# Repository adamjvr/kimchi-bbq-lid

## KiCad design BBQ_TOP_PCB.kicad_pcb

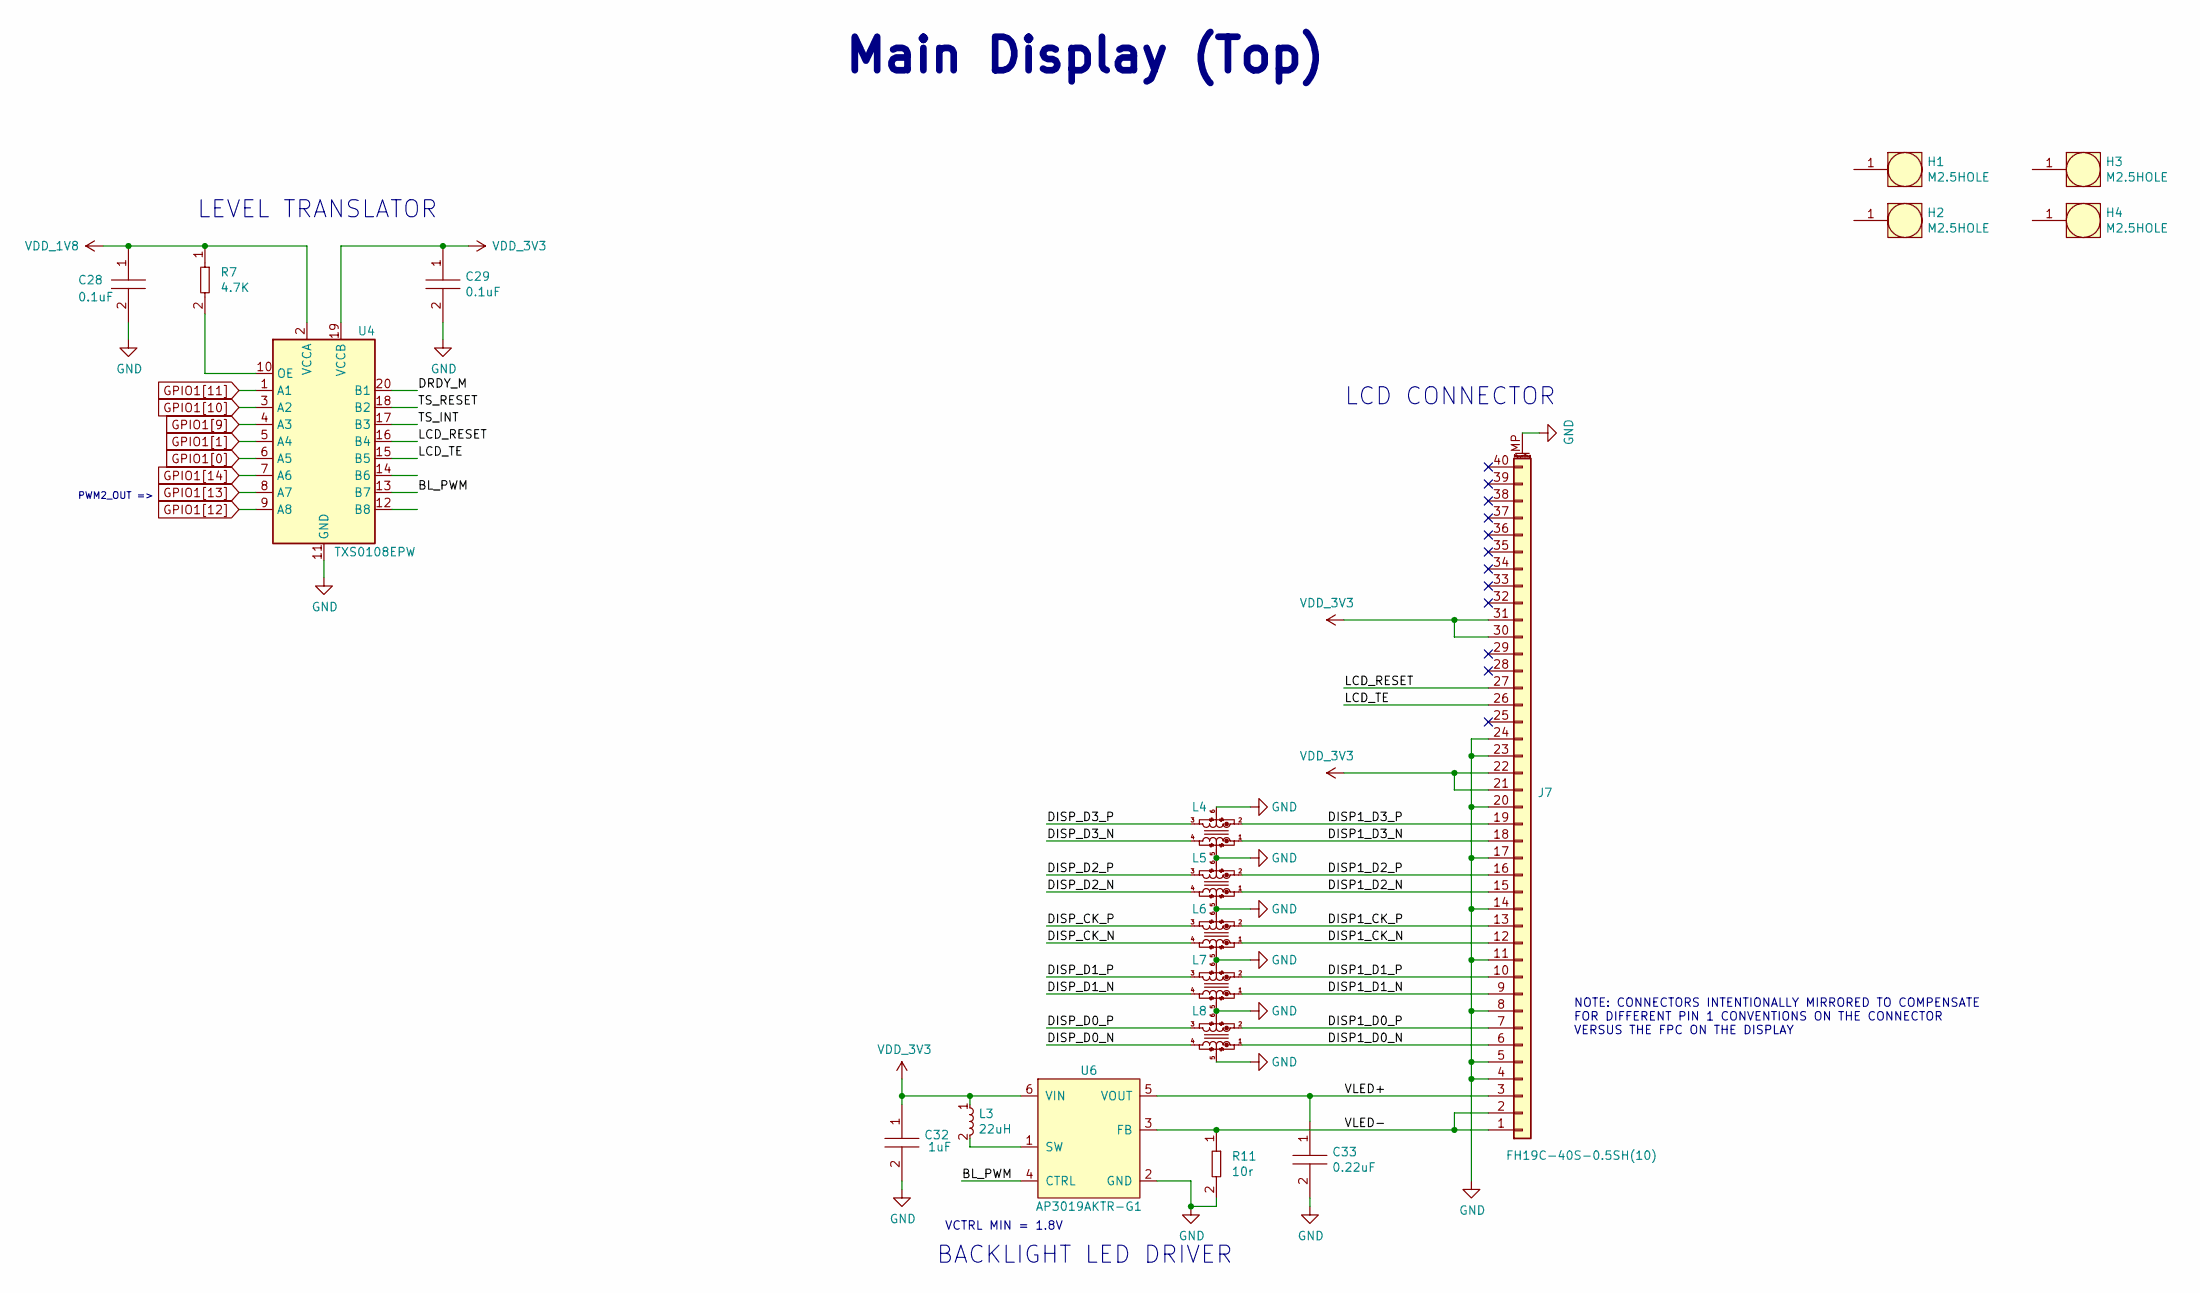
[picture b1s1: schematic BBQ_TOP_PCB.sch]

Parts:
C28, C29: C0603C104M5RACAUTO; C0603; Tolerance 20%; Voltage 50V; MFR# C0603C104M5RACAUTO
C32: C0603C105K4PAC7411; C0603; Tolerance 20%; Voltage 16V; MFR# C0603C105K4PAC7411
C33: CGA3E3X7R1H224K080AB; C0603; Tolerance 10%; Voltage 50V; MFR# CGA3E3X7R1H224K080AB
H1, H2, H3, H4: M2.5HOLE
J7: FH19C-40S-0.5SH(10); HRS_FH19C-40S-0.5SH_1x40-1MP_P0.50mm; Part FH19C-40S-0.5SH(10)
L3: TYA4012220M-10; L_Taiyo-Yuden_MD-4040; Tolerance *; Voltage *; MFR# TYA4012220M-10
L4, L5, L6, L7, L8: LCFE121002; Part LCFE121002
R7: RC0603JR-074K7L; R0603; Tolerance 1%; Voltage *; MFR# RC0603JR-074K7L
R11: RE0603FRE0710RL; R0603; Tolerance 1%; Voltage *; MFR# RE0603FRE0710RL
U4: TXS0108EPW; TXS0108EPWR; Part TXS0108EPW
U6: AP3019AKTR-G1; SOT-23-6_Handsoldering; Part AP3019AKTR-G1

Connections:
/BL_PWM: U4.13 (B7), U6.4 (CTRL)
/DISP1_CK_N: J7.12, L6.1
/DISP1_CK_P: J7.13, L6.2
/DISP1_D0_N: J7.6, L8.1
/DISP1_D0_P: J7.7, L8.2
/DISP1_D1_N: J7.9, L7.1
/DISP1_D1_P: J7.10, L7.2
/DISP1_D2_N: J7.15, L5.1
/DISP1_D2_P: J7.16, L5.2
/DISP1_D3_N: J7.18, L4.1
/DISP1_D3_P: J7.19, L4.2
/DISP_CK_N: L6.4
/DISP_CK_P: L6.3
/DISP_D0_N: L8.4
/DISP_D0_P: L8.3
/DISP_D1_N: L7.4
/DISP_D1_P: L7.3
/DISP_D2_N: L5.4
/DISP_D2_P: L5.3
/DISP_D3_N: L4.4
/DISP_D3_P: L4.3
/DRDY_M: U4.20 (B1)
/LCD_RESET: J7.27, U4.16 (B4)
/LCD_TE: J7.26, U4.15 (B5)
/TS_INT: U4.17 (B3)
/TS_RESET: U4.18 (B2)
/VLED+: C33.1, J7.3, U6.5 (VOUT)
/VLED-: J7.1, J7.2, R11.1, U6.3 (FB)
GND: C28.2, C29.2, C32.2, C33.2, J7.4, J7.5, J7.8, J7.11, J7.14, J7.17, J7.20, J7.23, J7.24, J7.MP (MountPin), L4.5, L4.6 (5), L5.5, L5.6 (5), L6.5, L6.6 (5), L7.5, L7.6 (5), L8.5, L8.6 (5), R11.2, U4.11 (GND), U6.2 (GND)
GPIO1[0]: U4.6 (A5)
GPIO1[1]: U4.5 (A4)
GPIO1[9]: U4.4 (A3)
GPIO1[10]: U4.3 (A2)
GPIO1[11]: U4.1 (A1)
GPIO1[12]: U4.9 (A8)
GPIO1[13]: U4.8 (A7)
GPIO1[14]: U4.7 (A6)
unnamed: L3.2, U6.1 (SW)
unnamed: R7.2, U4.10 (OE)
VDD_1V8: C28.1, R7.1, U4.2 (VCCA)
VDD_3V3: C29.1, C32.1, J7.21, J7.22, J7.30, J7.31, L3.1, U4.19 (VCCB), U6.6 (VIN)

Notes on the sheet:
BACKLIGHT LED DRIVER
VCTRL MIN = 1.8V
LCD CONNECTOR
NOTE: CONNECTORS INTENTIONALLY MIRRORED TO COMPENSATE FOR DIFFERENT PIN 1 CONVENTIONS ON THE CONNECTOR VERSUS THE FPC ON THE DISPLAY
LEVEL TRANSLATOR
PWM2_OUT =>
Main Display (Top)

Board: 2 copper layers, 19 parts (15 on the bottom side), 20 nets, no tracks yet.

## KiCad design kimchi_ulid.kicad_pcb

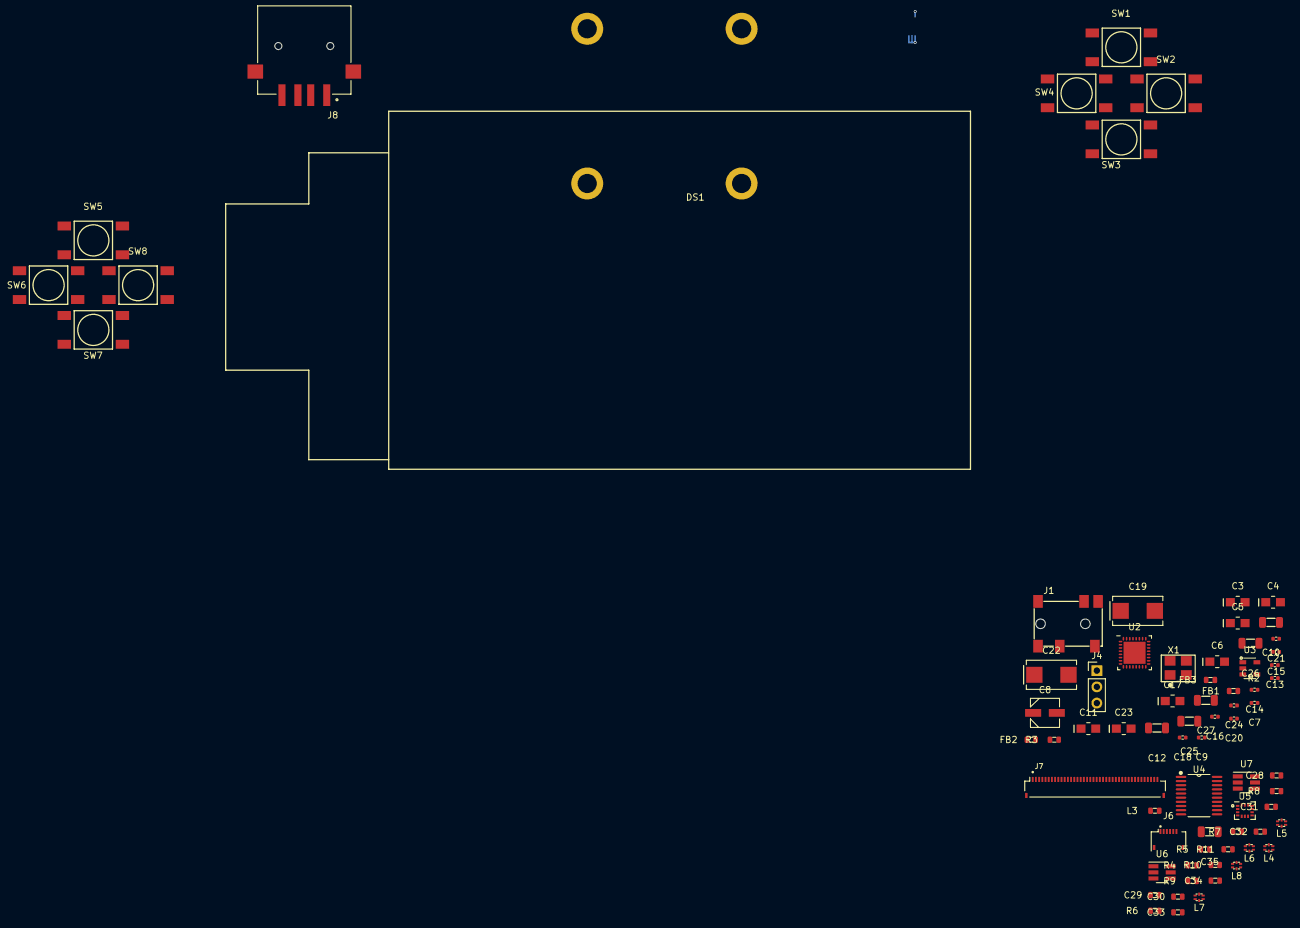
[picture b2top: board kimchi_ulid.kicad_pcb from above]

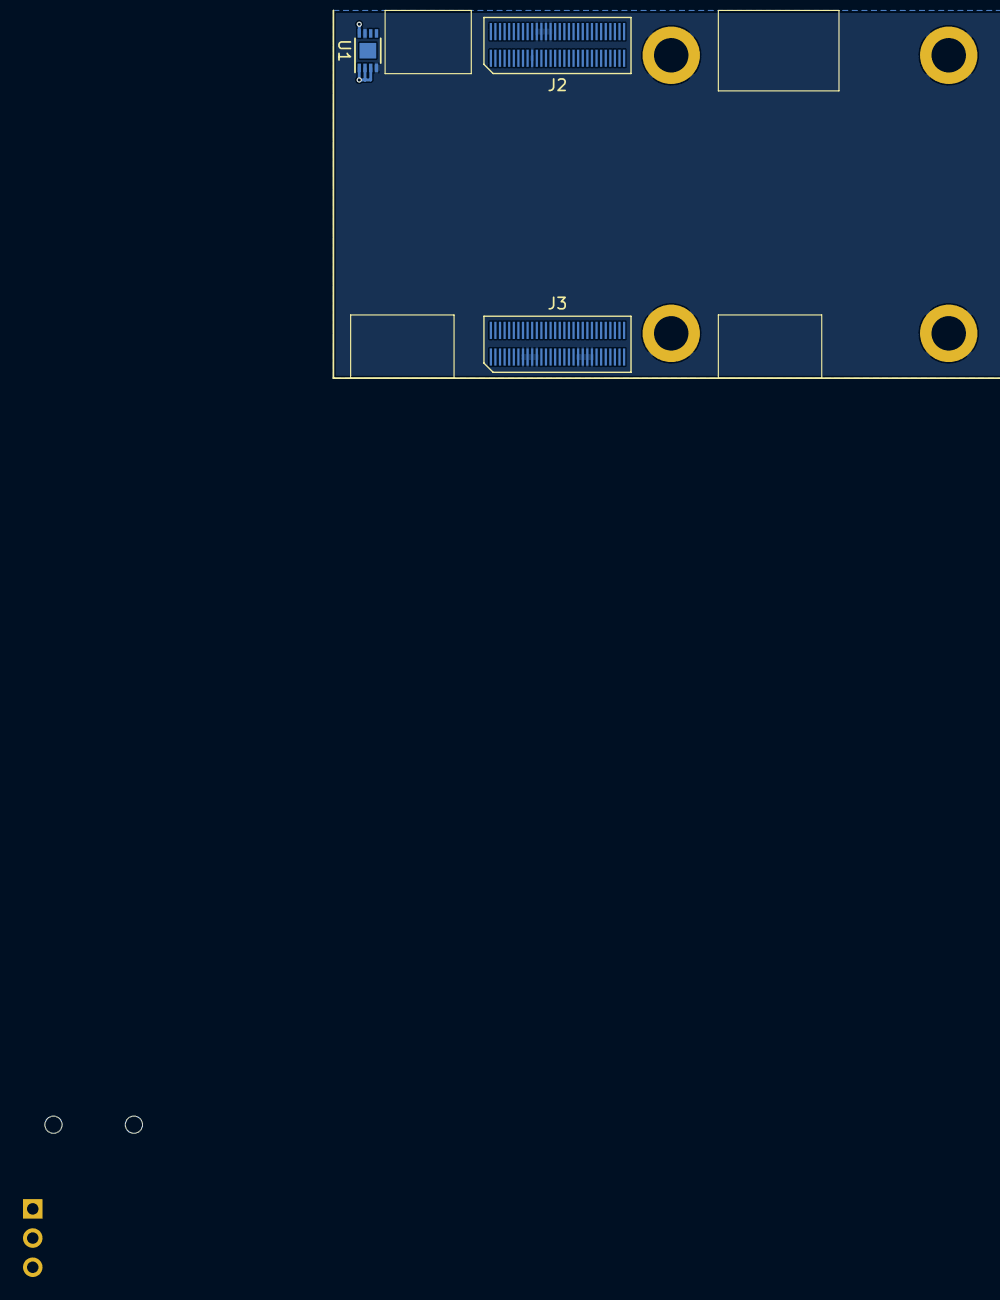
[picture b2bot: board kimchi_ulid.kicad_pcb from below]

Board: 4 copper layers, 83 parts (6 on the bottom side), 69 nets.

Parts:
C3, C4, C5, C6, C11, C17, C23: T494A106M006AT
C7, C9, C13, C14, C15, C16, C18, C20, C21, C24: C0402C104K9PACTU; C0402
C8: UZP1H0R1MCL1GB
C10, C12, C25, C26, C27: T491A105K010AT; C1206
C19, C22: T491D227M010AT
C28, C29, C30, C34: C0603C104M5RACAUTO; C0603
C31: CL10A106MP8NNNC; C0603
C32: C0603C105K4PAC7411; C0603
C33: CGA3E3X7R1H224K080AB; C0603
C35: CC1206MKX5R5BB107; C1206
DS1: ER-TFT035-6; ER-TFT035-6_LCD_DISPLAY
FB1, FB2, FB3: FBMJ1608HM180NTR; R0603
H1, H2, H3, H4: MountingHole_Pad; MountingHole_3mm_Pad
J1: 54-00177
J2, J3: DF40HC(3.5)-60DS
J4: Conn_01x03_Male; Pin_Header_Straight_1x03_Pitch2.54mm
J6: H19C-6S-0.5SH; HRS_FH19C-6S-0.5SH_1x06-1MP_P0.50mm
J7: FH19C-40S-0.5SH(10); HRS_FH19C-40S-0.5SH_1x40-1MP_P0.50mm
J8: 1-292303-6; TE_1-292303-6
L1: GG_LOGO; groupgets_logo
L2: OSHPARK_LOGO; oshpark_logo
L3: TYA4012220M-10; R0603
L4, L5, L6, L7, L8: LCFE121002
LOGO1: Logo_Open_Hardware_Small; OSHW-Logo_5.7x6mm_SilkScreen
R2: RC0402JR-072K2L; R0402
R3: RC0603FR-0747KL; R0603
R4, R5, R6, R7, R8, R9, R10: RC0603JR-074K7L; R0603
R11: RE0603FRE0710RL; R0603
SW1, SW2, SW3, SW4, SW5, SW6, SW7, SW8: TL3301NF260QG
U1: 24C32; DFN-8-1EP_3x2mm_P0.5mm_EP1.36x1.46mm
U2: WM8750CJLGEFL; QFN-32_EP_5x5_Pitch0.5mm
U3: SN74LV1T34DBVRG4; SOT-23-5
U4: TXS0108EPW; TXS0108EPWR
U5: LSM6DSRTR
U6: AP3019AKTR-G1; SOT-23-6_Handsoldering
U7: TPD3S014; SOT-23-6_Handsoldering
X1: ASFL1-12.288MHZ-EC-T; ASFL1

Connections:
/Main Display /BL_PWM: U4.13, U6.4
/Main Display /DISP1_CK_N: J7.12, L6.1
/Main Display /DISP1_CK_P: J7.13, L6.2
/Main Display /DISP1_D0_N: J7.6, L8.1
/Main Display /DISP1_D0_P: J7.7, L8.2
/Main Display /DISP1_D1_N: J7.9, L7.1
/Main Display /DISP1_D1_P: J7.10, L7.2
/Main Display /DISP1_D2_N: J7.15, L5.1
/Main Display /DISP1_D2_P: J7.16, L5.2
/Main Display /DISP1_D3_N: J7.18, L4.1
/Main Display /DISP1_D3_P: J7.19, L4.2
/Main Display /INT1A_G: U4.12, U5.9
/Main Display /INT_M: U4.14, U5.4
/Main Display /LCD_RESET: J7.27, U4.16
/Main Display /LCD_TE: J7.26, U4.15
/Main Display /TS_INT: J6.3, U4.17
/Main Display /TS_RESET: J6.4, U4.18
/Main Display /VLED+: C33.1, J7.3, U6.5
/Main Display /VLED-: J7.1, J7.2, R11.1, U6.3
GND: C3.2, C4.2, C5.2, C6.2, C7.2, C8.2, C9.2, C11.2, C13.2, C14.2, C15.2, C16.2, C17.2, C18.2, C20.2, C21.2, C23.2, C24.2, C28.2, C29.2, C30.2, C31.2, C32.2, C33.2, C34.2, C35.2, FB3.1, H1.1, H2.1, H3.1, H4.1, J2.11, J2.12, J2.13, J2.14, J2.51, J3.38, J3.39, J3.40, J3.41, J3.50, J3.51, J3.52, J3.53, J6.1, J6.MP, J7.4, J7.5, J7.8, J7.11, J7.14, J7.17, J7.20, J7.23, J7.24, J7.MP, J8.4, J8.SH1, J8.SH2, L4.5, L4.6, L5.5, L5.6, L6.5, L6.6, L7.5, L7.6, L8.5, L8.6, R3.1, R11.2, U1.4, U1.7, U2.4, U2.14, U2.19, U2.29, U2.33, U3.3, U4.11, U5.6, U5.7, U6.2, U7.2, X1.2
GPIO1[0]: J3.30, U4.6
GPIO1[1]: J3.29, U4.5
GPIO1[9]: J3.28, U4.4
GPIO1[10]: J3.27, U4.3
GPIO1[11]: J3.26, U4.1
GPIO1[12]: J3.25, U4.9
GPIO1[13]: J3.24, U4.8
GPIO1[14]: J3.23, U4.7
I2C3_SCL: J2.18, J6.5, R10.2, U2.32, U5.13
I2C3_SDA: J2.17, J6.6, R9.2, U2.31, U5.14
I2C4_SCL: J2.16, U1.6
I2C4_SDA: J2.15, U1.5
MCLK: J4.3, U3.4
MIC_BIAS: C9.1, C11.1, R2.2, U2.22
MIC_IN: C25.1, U2.23
unnamed: C10.1, U2.28
unnamed: C12.1, U2.27
unnamed: C15.1, C17.1, U2.21
unnamed: C19.1, U2.13
unnamed: C19.2, J1.4
unnamed: C20.1, C23.1, U2.20
unnamed: C22.1, U2.12
unnamed: C22.2, J1.3
unnamed: C25.2, J1.2, R2.1, R3.2
unnamed: C26.1, U2.16
unnamed: C27.1, U2.15
unnamed: FB3.2, J1.1
unnamed: J4.2, U2.1
unnamed: L3.2, U6.1
unnamed: R4.2, U5.2
unnamed: R5.2, U5.3
unnamed: R6.2, U5.1
unnamed: R7.2, U4.10
unnamed: R8.2, U5.12
unnamed: U3.2, X1.3
SAI3_MCLK: J3.37, J4.1
SAI3_RXD: J3.33, U2.8
SAI3_RXFS: J3.34, U2.9
SAI3_TXC: J3.31, U2.5
SAI3_TXD: J3.32, U2.6
SAI3_TXFS: J3.36, U2.7
USB2_DN: J2.59, J8.2, U7.6
USB2_DP: J2.60, J8.3, U7.5
VBUS: C35.1, J8.1, U7.4
VDD: C6.1, C7.1, C13.1, C18.1, C21.1, C24.1, FB2.2, U2.2, U2.3, U3.5, X1.4
VDDA: C5.1, C8.1, C14.1, C16.1, FB1.2, U2.17, U2.18
VDD_1V8: C28.1, J3.42, J3.43, J3.44, J3.45, R7.1, U4.2
VDD_3V3: C3.1, C4.1, C29.1, C30.1, C31.1, C32.1, FB1.1, FB2.1, J3.54, J3.55, J3.56, J3.57, J6.2, J7.21, J7.22, J7.30, J7.31, L3.1, R4.1, R5.1, R6.1, R8.1, R9.1, R10.1, U1.1, U1.2, U1.3, U1.8, U4.19, U5.5, U5.8, U6.6
VDD_5V: C34.1, J2.7, J2.8, J2.9, J2.10, U7.1, U7.3

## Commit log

2020-12-10 added resistors for codec, transferring workstations
2020-12-11 Oscillator Circuit
    Oscillator circuit and related components added to the codec circuit. These may be unnecessary but are pending review.
2020-12-12 removing wrong file
    wrong file removed.
2021-01-29 Design Refactor and Major Progress
    Refactored the design of the lid, integrated the schematics from the Display lid, and the HiFi lid. Changed PCB shape to reflect change to dual screen design. Found SPI TFT display for bottom display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
2021-02-24 Two Projects
    Created a dedicated project for the upper screen PCB, I moved the IMU and USB A host circuits to their own schematic page and made them part of the PCB project for the bottom half PCB that holds the 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

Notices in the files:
parts and their libraries:
Copyright 2016 Accelerated Designs. All rights reserved.
